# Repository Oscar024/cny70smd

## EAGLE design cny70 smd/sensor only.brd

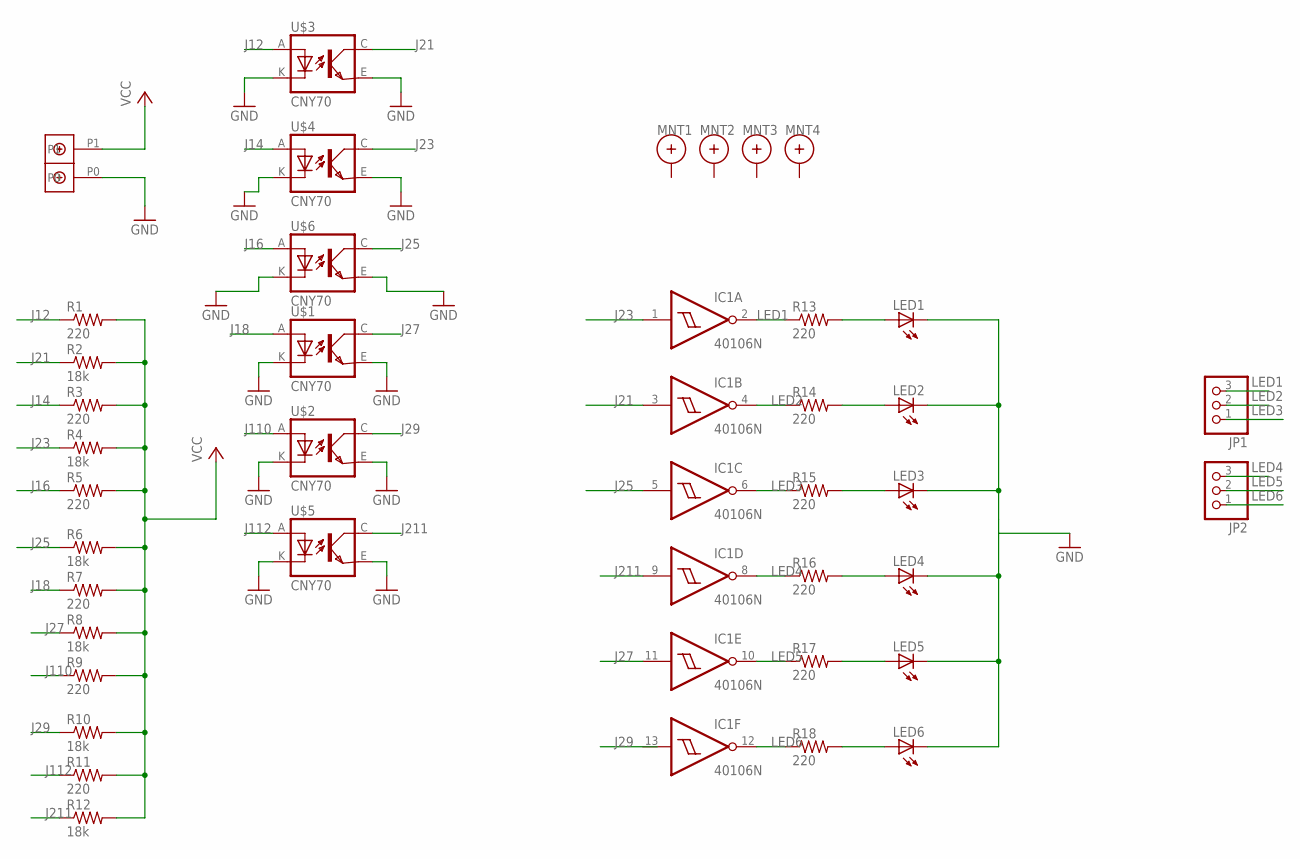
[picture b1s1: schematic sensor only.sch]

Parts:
IC1: 40106N; DIL14
JP1, JP2: PINHD-1X3; 1X03
LED1, LED2, LED3, LED4, LED5, LED6: LEDCHIPLED_1206; CHIPLED_1206
MNT1, MNT2, MNT3, MNT4: HOLE_MNT_0.135; HOLE_MNT_#5-40
R1, R3, R5, R7, R9, R11, R13, R14, R15, R16, R17, R18: 220; M1206
R2, R4, R6, R8, R10, R12: 18k; M1206
U$1, U$2, U$3, U$4, U$5, U$6: CNY70; 4
U$7: DBCONN-1X2

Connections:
GND: LED1.C, LED2.C, LED3.C, LED4.C, LED5.C, LED6.C, U$1.E (EMI), U$1.K (C), U$2.E (EMI), U$2.K (C), U$3.E (EMI), U$3.K (C), U$4.E (EMI), U$4.K (C), U$5.E (EMI), U$5.K (C), U$6.E (EMI), U$6.K (C), U$7.P0
J12: R1.1, U$3.A
J14: R3.1, U$4.A
J16: R5.1, U$6.A
J18: R7.1, U$1.A
J21: IC1.3 (I), R2.1, U$3.C (COL)
J23: IC1.1 (I), R4.1, U$4.C (COL)
J25: IC1.5 (I), R6.1, U$6.C (COL)
J27: IC1.11 (I), R8.1, U$1.C (COL)
J29: R10.1, U$2.C (COL)
J110: R9.1, U$2.A
J112: R11.1, U$5.A
J211: IC1.9 (I), R12.1, U$5.C (COL)
LED1: IC1.2 (O), JP1.3, R13.1
LED2: IC1.4 (O), JP1.2, R14.1
LED3: IC1.6 (O), JP1.1, R15.1
LED4: IC1.8 (O), JP2.3, R16.1
LED5: IC1.10 (O), JP2.2, R17.1
LED6: IC1.12 (O), JP2.1, R18.1
unnamed: LED1.A, R13.2
unnamed: LED2.A, R14.2
unnamed: LED3.A, R15.2
unnamed: LED4.A, R16.2
unnamed: LED5.A, R17.2
unnamed: LED6.A, R18.2
VCC: R1.2, R2.2, R3.2, R4.2, R5.2, R6.2, R7.2, R8.2, R9.2, R10.2, R11.2, R12.2, U$7.P1
VDD: IC1.14 (VDD)
VSS: IC1.7 (VSS)

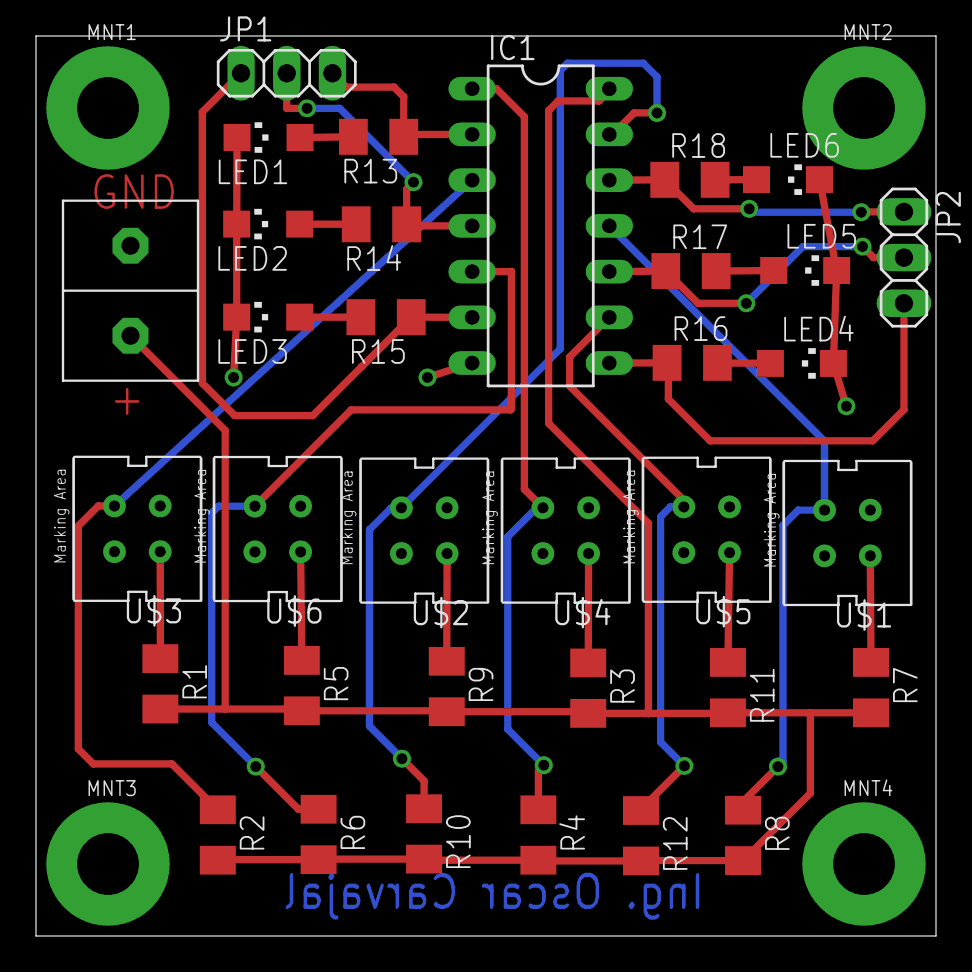
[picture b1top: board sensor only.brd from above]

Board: 2 copper layers, 50.0 x 50.0 mm, 38 parts (0 on the bottom side), 26 nets.
